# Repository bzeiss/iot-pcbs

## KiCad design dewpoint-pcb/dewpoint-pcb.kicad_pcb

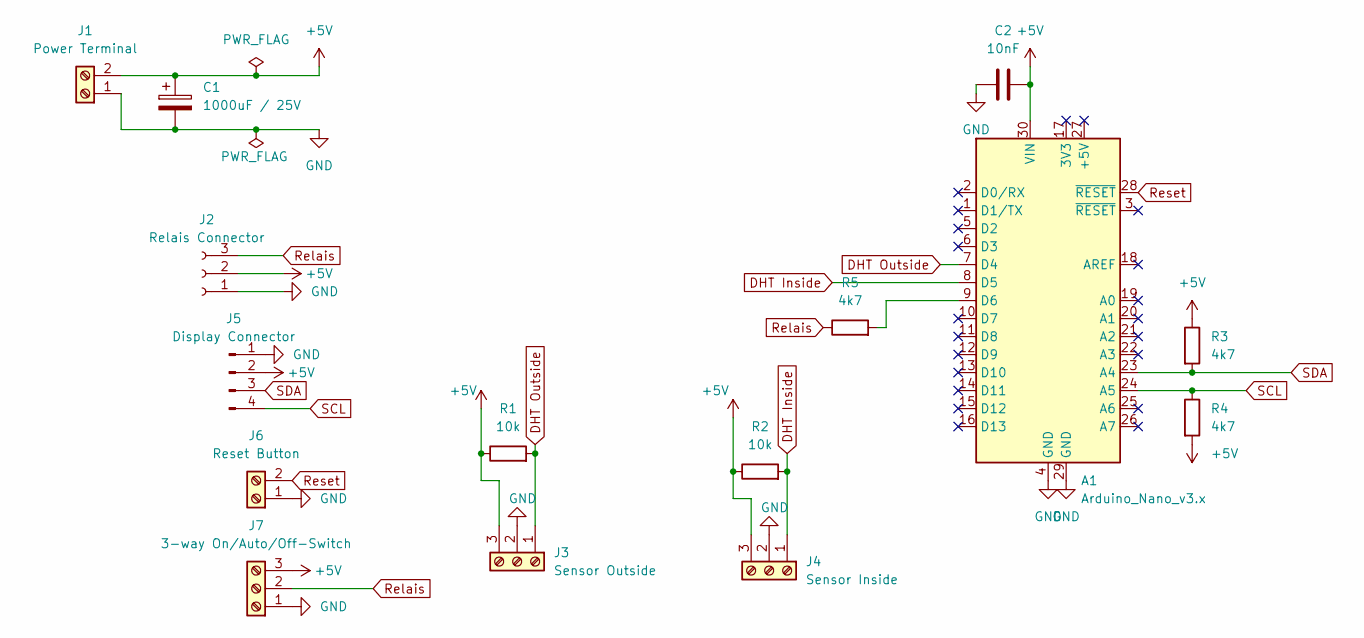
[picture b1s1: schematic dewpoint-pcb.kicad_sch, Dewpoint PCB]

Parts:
A1: Arduino_Nano_v3.x; Arduino_Nano
C1: 1000uF / 25V; CP_Radial_D10.0mm_P7.50mm
C2: 10nF; C_Disc_D4.7mm_W2.5mm_P5.00mm
J1: Power Terminal; TerminalBlock_Phoenix_MKDS-1,5-2_1x02_P5.00mm_Horizontal
J2: Relais Connector; PinSocket_1x03_P2.54mm_Horizontal
J3: Sensor Outside; TerminalBlock_Phoenix_MKDS-1,5-3_1x03_P5.00mm_Horizontal
J4: Sensor Inside; TerminalBlock_Phoenix_MKDS-1,5-3_1x03_P5.00mm_Horizontal
J5: Display Connector; PinHeader_1x04_P2.54mm_Vertical
J6: Reset Button; TerminalBlock_Phoenix_MKDS-1,5-2_1x02_P5.00mm_Horizontal
J7: 3-way On/Auto/Off-Switch; TerminalBlock_Phoenix_MKDS-1,5-3_1x03_P5.00mm_Horizontal
R1, R2: 10k; R_Axial_DIN0207_L6.3mm_D2.5mm_P10.16mm_Horizontal
R3, R4, R5: 4k7; R_Axial_DIN0207_L6.3mm_D2.5mm_P10.16mm_Horizontal

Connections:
+5V: A1.30 (VIN), C1.1, C2.2, J1.2, J2.2, J3.3, J4.3, J5.2, J7.3, R1.1, R2.1, R3.1, R4.2
DHT Inside: A1.8 (D5), J4.1, R2.2
DHT Outside: A1.7 (D4), J3.1, R1.2
GND: A1.4 (GND), A1.29 (GND), C1.2, C2.1, J1.1, J2.1, J3.2, J4.2, J5.1, J6.1, J7.1
unnamed: A1.9 (D6), R5.2
Relais: J2.3, J7.2, R5.1
Reset: A1.28 (~RESET), J6.2
SCL: A1.24 (A5), J5.4, R4.1
SDA: A1.23 (A4), J5.3, R3.2

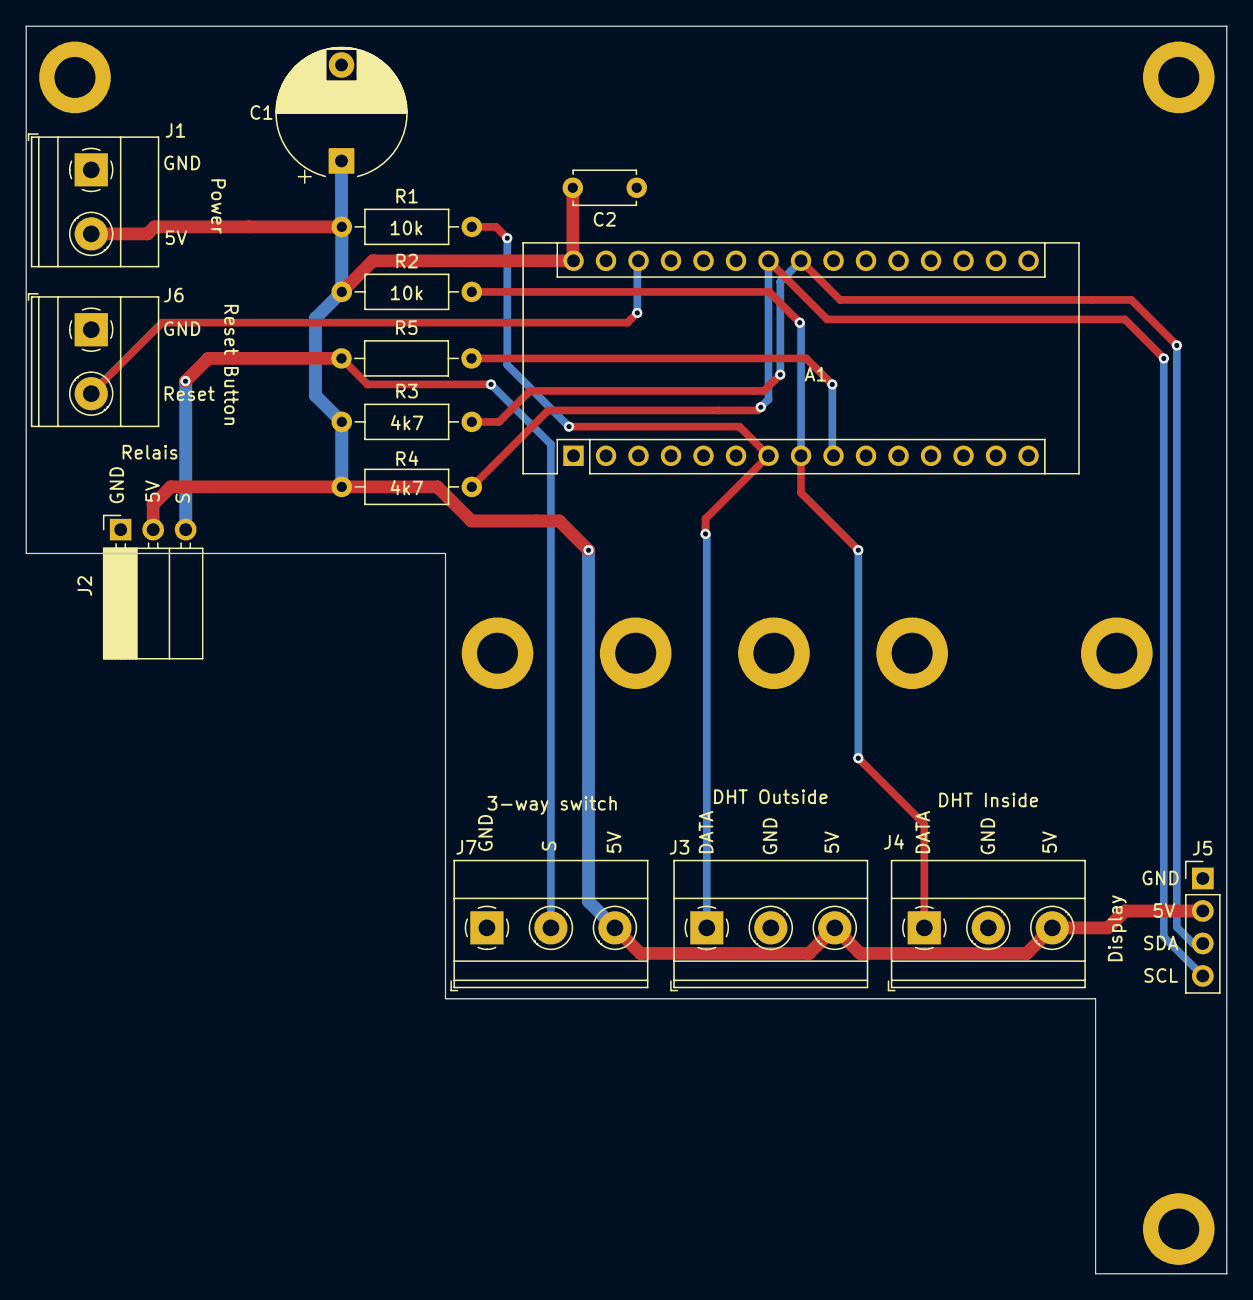
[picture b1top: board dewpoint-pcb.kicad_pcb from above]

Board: 2 copper layers, 93.8 x 97.5 mm, 15 parts (0 on the bottom side), 9 nets.

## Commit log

2022-06-10 initial unrouted dewpoint pcb version for BOPLA ET-214 Gehäuse Serie Euromas II, 200 x 120 x 57 mm, IP65
2022-06-10 removed unnecessary symbols
2022-06-12 v1.0, gerber.zip
2022-06-12 updated pcb gerber
2022-06-23 Correction, Relais switch wasn't connected correctly.
2023-03-31 work on a new board
